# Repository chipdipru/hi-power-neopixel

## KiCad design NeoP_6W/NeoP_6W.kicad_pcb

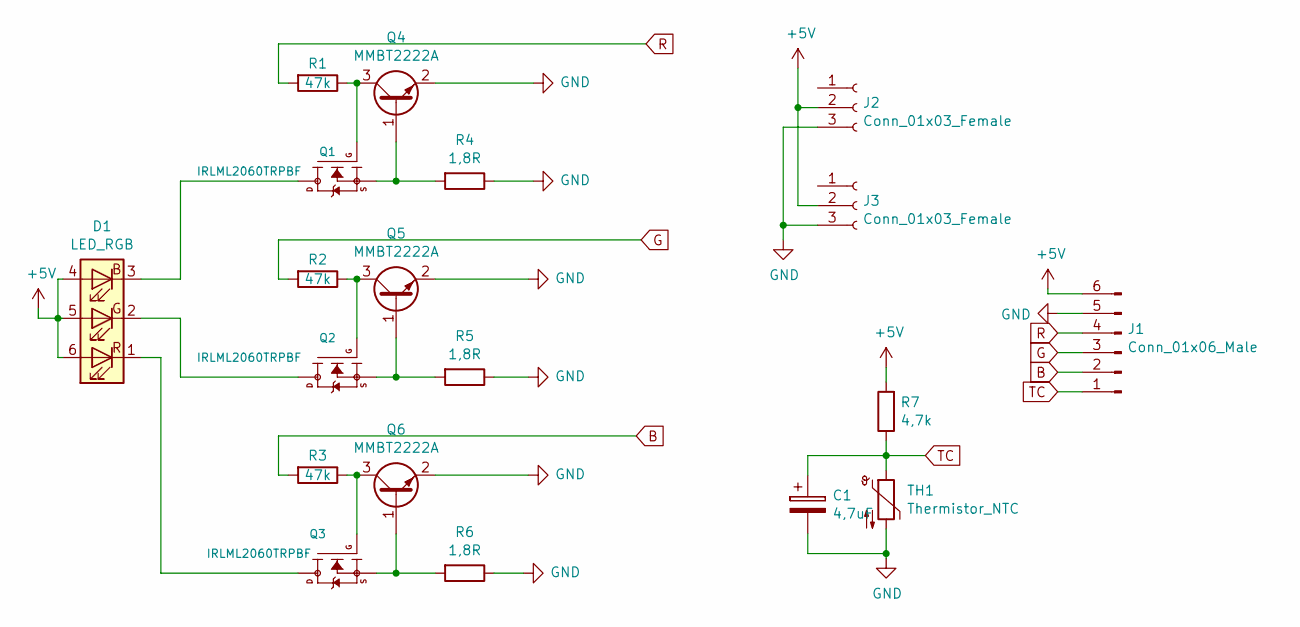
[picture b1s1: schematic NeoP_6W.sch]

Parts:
C1: 4,7uF; CP_EIA-3216-18_Kemet-A_Pad1.58x1.35mm_HandSolder
D1: LED_RGB; LED_RGB_Getian_GT-P6PRGB4303
J1: Conn_01x06_Male; Pin_Header_Straight_1x06
J2, J3: Conn_01x03_Female; Socket_Strip_Straight_1x03
Q1, Q2, Q3: IRLML2060TRPBF; SOT-23
Q4, Q5, Q6: MMBT2222A; SOT-23
R1, R2, R3: 47k; R_0603_1608Metric_Pad1.05x0.95mm_HandSolder
R4, R5, R6: 1,8R; R_1206_HandSoldering
R7: 4,7k; R_0603_1608Metric_Pad1.05x0.95mm_HandSolder
TH1: Thermistor_NTC; R_0603_1608Metric_Pad1.05x0.95mm_HandSolder

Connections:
+5V: D1.4 (BA), D1.5 (GA), D1.6 (RA), J1.6, J2.2, J3.2, R7.2
B: J1.2, R3.2
G: J1.3, R2.2
GND: C1.2, J1.5, J2.3, J3.3, Q4.2 (C), Q5.2 (C), Q6.2 (C), R4.1, R5.1, R6.1, TH1.2
unnamed: D1.1 (RK), Q3.3 (D)
unnamed: D1.2 (GK), Q2.3 (D)
unnamed: D1.3 (BK), Q1.3 (D)
unnamed: Q1.1 (G), Q4.3 (E), R1.1
unnamed: Q1.2 (S), Q4.1 (B), R4.2
unnamed: Q2.1 (G), Q5.3 (E), R2.1
unnamed: Q2.2 (S), Q5.1 (B), R5.2
unnamed: Q3.1 (G), Q6.3 (E), R3.1
unnamed: Q3.2 (S), Q6.1 (B), R6.2
R: J1.4, R1.2
TC: C1.1, J1.1, R7.1, TH1.1

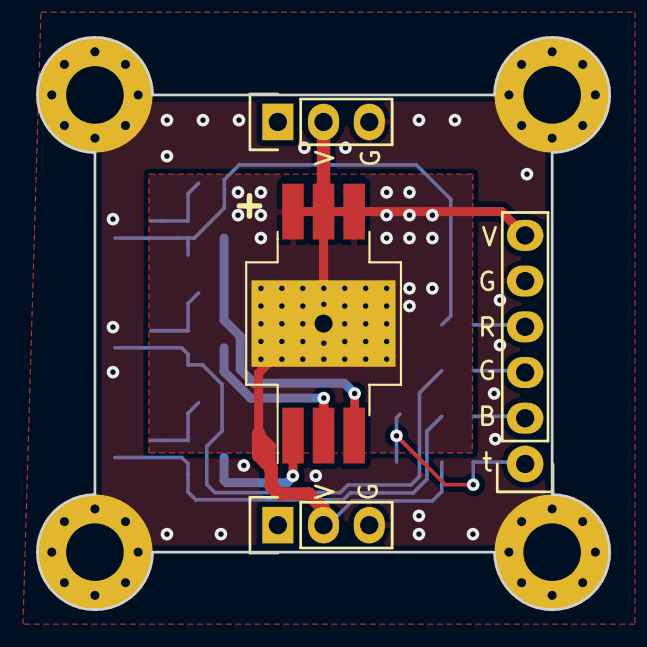
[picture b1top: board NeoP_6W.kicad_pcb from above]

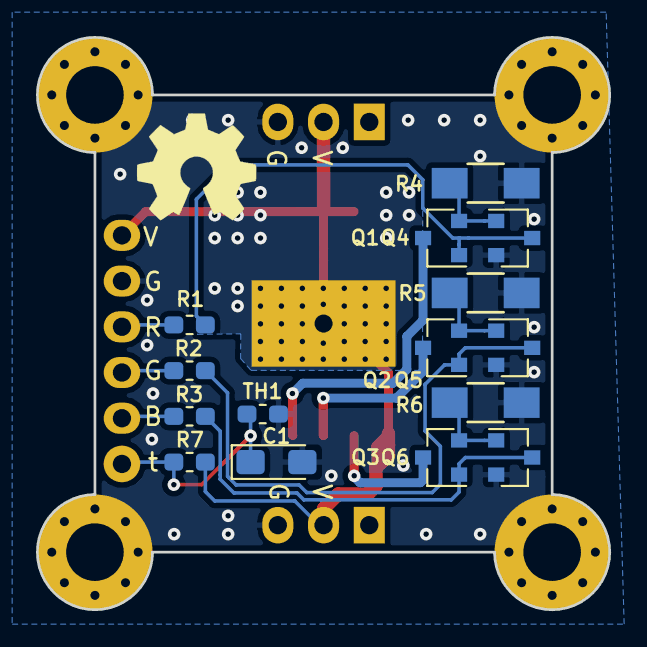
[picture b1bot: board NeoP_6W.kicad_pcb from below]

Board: 2 copper layers, 31.8 x 31.8 mm, 19 parts (15 on the bottom side), 15 nets.
